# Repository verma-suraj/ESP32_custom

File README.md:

# ESP32 Custom PCB — Team Circuitrix

A custom ESP32 PCB designed in KiCad.

## Repository Structure

```
ESP32_custom/       # KiCad schematic and PCB design files
  ├── *.kicad_sch   # Schematic
  ├── *.kicad_pcb   # PCB layout
  ├── *.kicad_pro   # Project file
  ├── *.kicad_dru   # Design rules
  └── Gerber File/  # Manufacturing files (Gerber + drill)
Bill of Materials/  # BOM in CSV and XLSX formats
demo/               # 3D board view video and PCB renders
```

## Demo

| Top View | Bottom View |
|----------|-------------|
|  |  |

A 3D walkthrough of the board is available in [demo/3D view of the Board.mp4](demo/3D%20view%20of%20the%20Board.mp4).

## Reference Datasheets

- [ESP32-WROOM-32E Datasheet](https://www.espressif.com/sites/default/files/documentation/esp32-wroom-32e_esp32-wroom-32ue_datasheet_en.pdf)
- [ESP32-S2-DevKitM-1 Schematic](https://dl.espressif.com/dl/schematics/ESP32-S2-DevKitM-1_V1_Schematics.pdf)
- [ESP32-DevKitC V4 Schematic](https://dl.espressif.com/dl/schematics/esp32_devkitc_v4-sch.pdf)

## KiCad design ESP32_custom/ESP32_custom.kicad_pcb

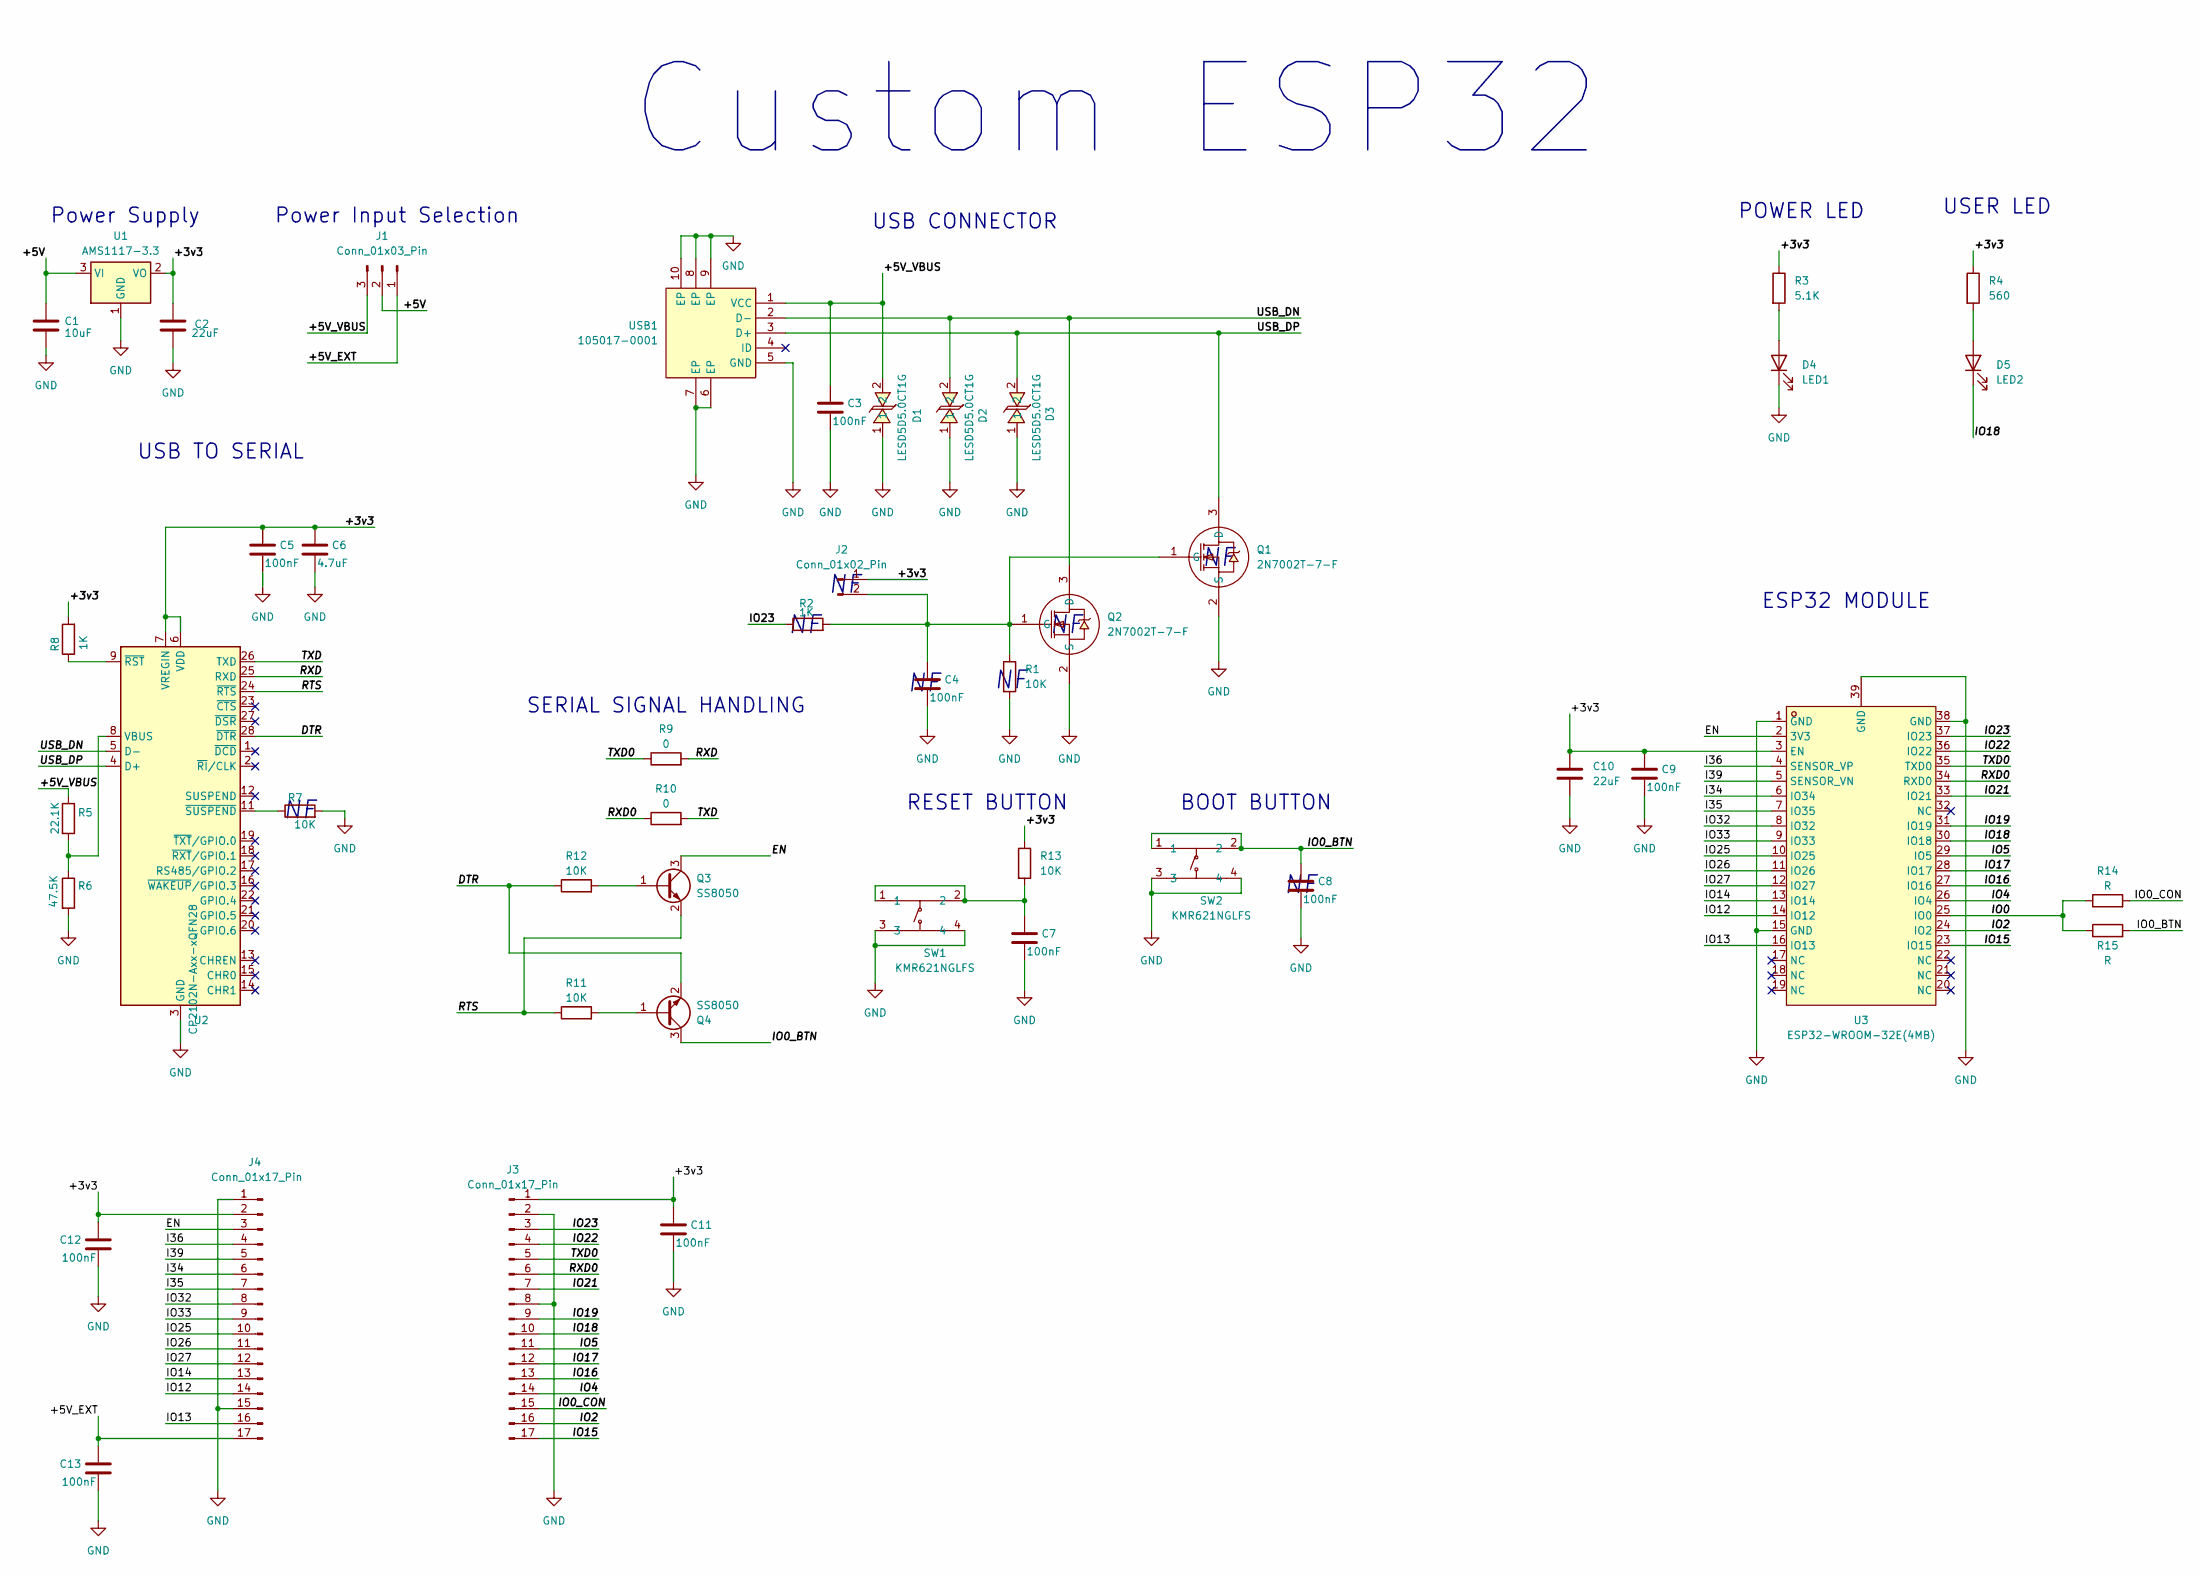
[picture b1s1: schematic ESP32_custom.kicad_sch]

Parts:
C1: 10uF; C_0402_1005Metric
C2: 22uF; C_0402_1005Metric
C3, C4, C5, C7, C8, C9, C11, C12, C13: 100nF; C_0402_1005Metric
C6: 4.7uF; C_0402_1005Metric
C10: 22uF; C_0805_2012Metric
D1, D2, D3: LESD5D5.0CT1G; SOD-523_L1.2-W0.8-LS1.6-BI; LCSC Part C5199850
D4: LED1; LED_0402_1005Metric
D5: LED2; LED_0402_1005Metric
J1: Conn_01x03_Pin; PinHeader_1x03_P2.54mm_Vertical
J2: Conn_01x02_Pin; PinHeader_1x02_P2.54mm_Vertical
J3, J4: Conn_01x17_Pin; PinHeader_1x17_P2.54mm_Vertical
Q1, Q2: 2N7002T-7-F; SOT-523-3_L1.6-W0.8-P1.00-LS1.6-BR; LCSC Part C139445
Q3, Q4: SS8050; SOT-23
R1, R7, R11, R12, R13: 10K; R_0402_1005Metric
R2, R8: 1K; R_0402_1005Metric
R3: 5.1K; R_0402_1005Metric
R4: 560; R_0402_1005Metric
R5: 22.1K; R_0402_1005Metric
R6: 47.5K; R_0402_1005Metric
R9, R10: 0; R_0402_1005Metric
R14, R15: R; R_0402_1005Metric
SW1, SW2: KMR621NGLFS; KEY-SMD_4P-L4.2-W2.8-P1.60-LS4.6; LCSC Part C221692
U1: AMS1117-3.3; SOT-223-3_TabPin2
U2: CP2102N-Axx-xQFN28; QFN-28-1EP_5x5mm_P0.5mm_EP3.35x3.35mm
U3: ESP32-WROOM-32E(4MB); WIFI-SMD_ESP32-WROOM-32E; LCSC Part C701341
USB1: 105017-0001; MICRO-USB-SMD_105017-0001; LCSC Part C136000

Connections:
/+3v3: C2.1, C5.1, C6.1, C9.1, C10.1, C11.1, C12.1, J2.1, J3.1, J4.2, R3.1, R4.1, R8.2, R13.1, U1.2 (VO), U2.6 (VDD), U2.7 (VREGIN), U3.3 (EN)
/+5V: C1.1, J1.2, U1.3 (VI)
/+5V_EXT: C13.1, J1.1, J4.17
/+5V_VBUS: C3.1, D1.2, J1.3, R5.1, USB1.1 (VCC)
/DTR: Q4.2 (E), R12.1, U2.28 (~DTR)
/EN: J4.3, Q3.3 (C), U3.2 (3V3)
/I34: J4.6, U3.6 (IO34)
/I35: J4.7, U3.7 (IO35)
/I36: J4.4, U3.4 (SENSOR_VP)
/I39: J4.5, U3.5 (SENSOR_VN)
/IO0: R14.1, R15.1, U3.25 (IO0)
/IO0_BTN: C8.1, Q4.3 (C), R15.2, SW2.1, SW2.2
/IO0_CON: J3.15, R14.2
/IO2: J3.16, U3.24 (IO2)
/IO4: J3.14, U3.26 (IO4)
/IO5: J3.11, U3.29 (IO5)
/IO12: J4.14, U3.14 (IO12)
/IO13: J4.16, U3.16 (IO13)
/IO14: J4.13, U3.13 (IO14)
/IO15: J3.17, U3.23 (IO15)
/IO16: J3.13, U3.27 (IO16)
/IO17: J3.12, U3.28 (IO17)
/IO18: D5.1 (K), J3.10, U3.30 (IO18)
/IO19: J3.9, U3.31 (IO19)
/IO21: J3.7, U3.33 (IO21)
/IO22: J3.4, U3.36 (IO22)
/IO23: J3.3, R2.1, U3.37 (IO23)
/IO25: J4.10, U3.10 (IO25)
/IO26: J4.11, U3.11 (IO26)
/IO27: J4.12, U3.12 (IO27)
/IO32: J4.8, U3.8 (IO32)
/IO33: J4.9, U3.9 (IO33)
/RTS: Q3.2 (E), R11.1, U2.24 (~RTS)
/RXD: R9.2, U2.25 (RXD)
/RXD0: J3.6, R10.1, U3.34 (RXD0)
/TXD: R10.2, U2.26 (TXD)
/TXD0: J3.5, R9.1, U3.35 (TXD0)
/USB_DN: D2.2, Q2.3 (D), U2.5 (D-), USB1.2 (D-)
/USB_DP: D3.2, Q1.3 (D), U2.4 (D+), USB1.3 (D+)
GND: C1.2, C2.2, C3.2, C4.2, C5.2, C6.2, C7.2, C8.2, C9.2, C10.2, C11.2, C12.2, C13.2, D1.1, D2.1, D3.1, D4.1 (K), J3.2, J3.8, J4.1, J4.15, Q1.2 (S), Q2.2 (S), R1.2, R6.2, R7.2, SW1.3, SW1.4, SW2.3, SW2.4, U1.1 (GND), U2.3 (GND), U2.29 (GND), U3.1 (GND), U3.15 (GND), U3.38 (GND), U3.39 (GND), USB1.5 (GND), USB1.6 (EP), USB1.7 (EP), USB1.8 (EP), USB1.9 (EP), USB1.10 (EP)
unnamed: C7.1, R13.2, SW1.1, SW1.2
unnamed: D4.2 (A), R3.2
unnamed: D5.2 (A), R4.2
unnamed: C4.1, J2.2, Q1.1 (G), Q2.1 (G), R1.1, R2.2
unnamed: Q3.1 (B), R12.2
unnamed: Q4.1 (B), R11.2
unnamed: R5.2, R6.1, U2.8 (VBUS)
unnamed: R8.1, U2.9 (~RST)
unnamed: R7.1, U2.11 (~SUSPEND)

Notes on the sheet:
Power Supply
ESP32 MODULE
Custom ESP32
BOOT BUTTON
USB CONNECTOR
SERIAL SIGNAL HANDLING
POWER LED
RESET BUTTON
USER LED
Power Input Selection
USB TO SERIAL

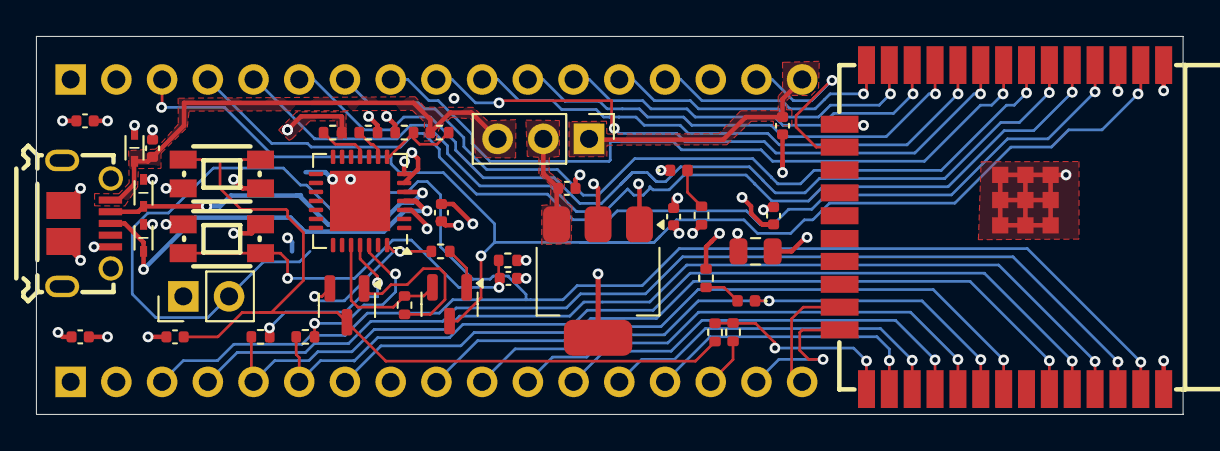
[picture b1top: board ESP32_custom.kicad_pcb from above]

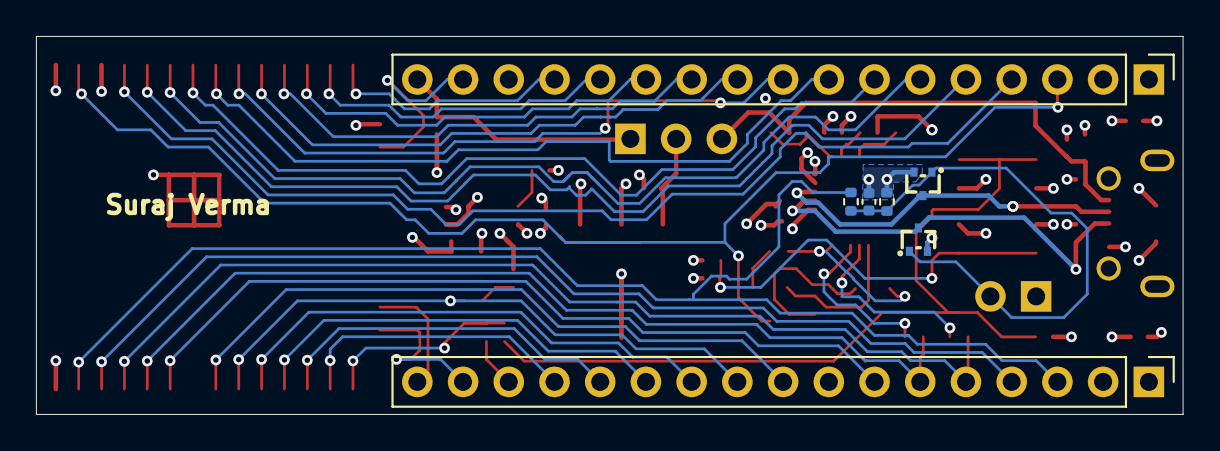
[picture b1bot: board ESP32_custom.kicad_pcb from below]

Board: 4 copper layers, 63.7 x 21.0 mm, 46 parts (7 on the bottom side), 49 nets.

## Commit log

2026-04-16 Initial commit: ESP32 custom PCB design (KiCad)
    Includes schematic, PCB layout, Gerber files, and BOM.
    Reference datasheets linked in README instead of stored in repo.
2026-04-16 Add demo folder with 3D board view and PCB renders
2026-04-16 Update README with demo section and board renders
